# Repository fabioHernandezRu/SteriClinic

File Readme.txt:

Explicacion:

Actas= archivos de acta de entregables.
GUI = Ultima actualizacion de la GUI.
HWD = Descripcion de hardware del sistema.
Linux Directory = Directorio que debe ponerse en el Linux Root .
PCB = Ultimas actualizaciones de la PCB
Software = Version Funcional de la Autoclave Pequeña

Novedades:
La interaccion ARM - Nextion y ARM-FPGA con la GUI es funcional al 99%, lo que quiere decir que solo faltan pruebas del sistema para pruebas de funcionalidad.
Todas las Alarmas estan seteadas y funcionan, por hw y por sw. 
Modificaciones al Menu de Mantenimiento.
Modificaciones a animaciones del sitema.
Sonido al Boot de Inicio.
Integracion al Datalogger, lo que quiere decir q todas las variables de Nextion son almacenables por el ARM en disco.
Acceso al menu de mantenimiento con total control de todos los elementos de la board(Valvulas, sensores, etc).

Videos: 
 boot --> https://youtu.be/RCzLulutQhg 
	(Ver con sonido)
 Explicaciones
	1) https://youtu.be/06hYOt6X7v8 --> Intro ARM y Nextion
	2) https://youtu.be/eV6HMTO3BoQ --> Intro ARM y Nextion 2
	3) --> Como crear un nuevo proyecto en base de las librerias.
	4) --> Estructura de archivos de linux para Autoclaves

Pendientes:

1) pruebas de este entregable.

Otros Pendientes:
1) Pagina web.

Solicitud: 
Disponibilidad del Ing. Peter para guiarlo en el proceso de montaje de las tarjetas en la Autoclave pequeña y ademas de la prueba de control

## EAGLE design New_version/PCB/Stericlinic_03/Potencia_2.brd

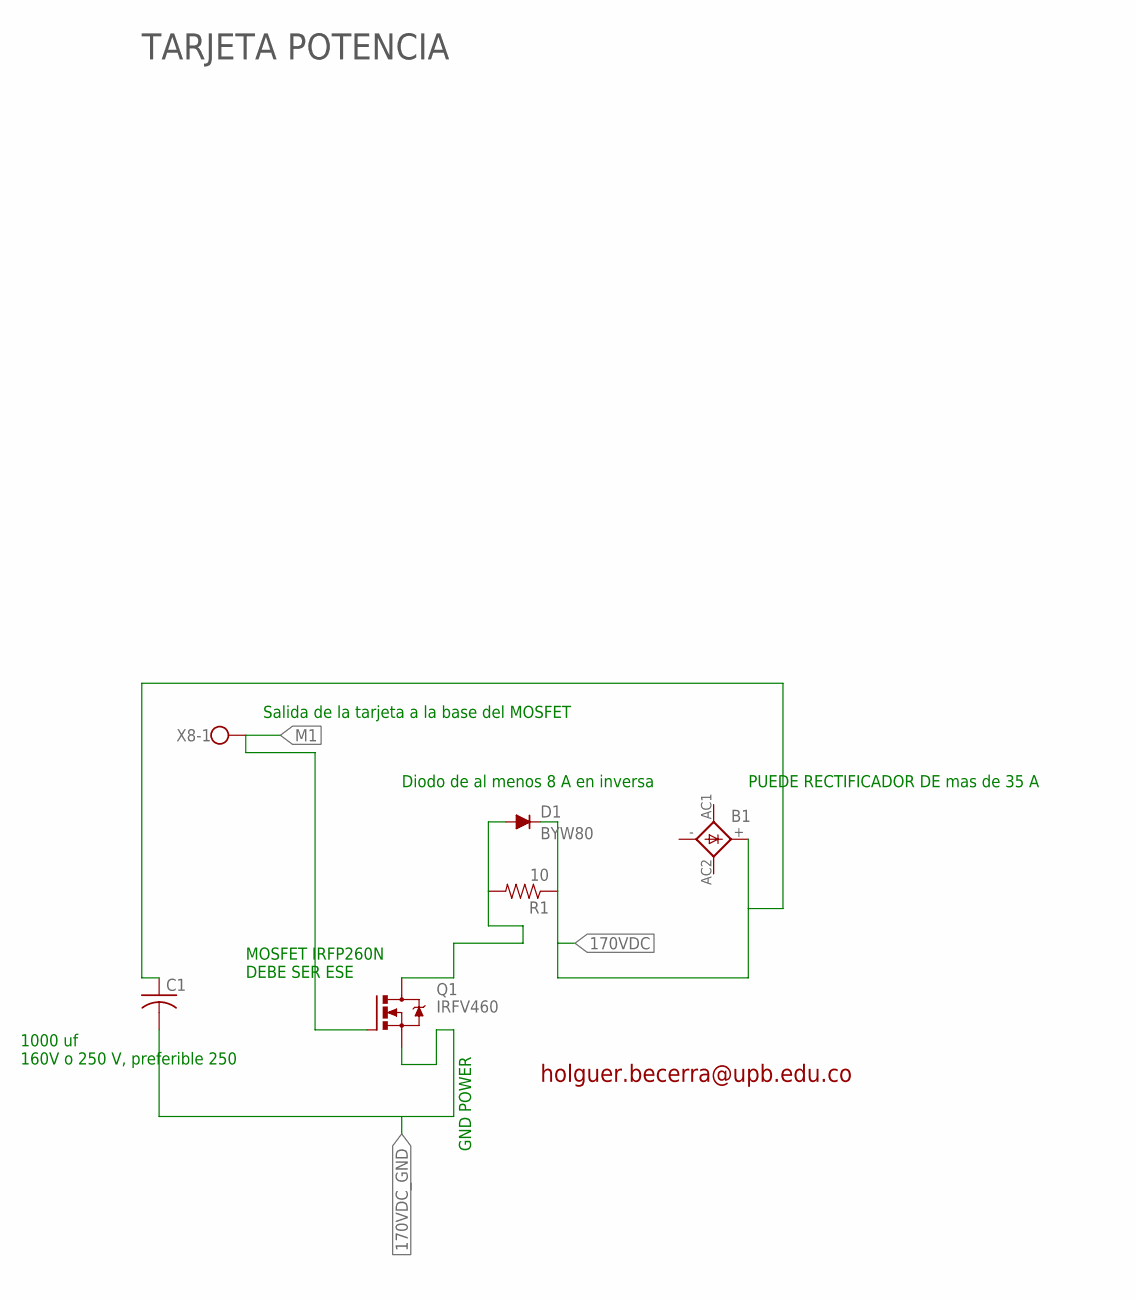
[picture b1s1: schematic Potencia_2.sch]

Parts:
B1: GBPC80X
C1: C-US275-205X316; C275-205X316
D1: BYW80; TO220ACS
Q1: IRFV460; TO258AA
R1: 10; 0603-RES
X8: CBE2; BE2

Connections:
170VDC: B1.+, C1.1, D1.C, R1.1
170VDC_GND: C1.2, Q1.2-S (S)
DAS: D1.A, Q1.1-D (D), R1.2
M1: Q1.3-G (G), X8.1

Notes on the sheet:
holguer.becerra@upb.edu.co
GND POWER
TARJETA POTENCIA
1000 uf 160V o 250 V, preferible 250
Diodo de al menos 8 A en inversa
MOSFET IRFP260N DEBE SER ESE
Salida de la tarjeta a la base del MOSFET
PUEDE RECTIFICADOR DE mas de 35 A

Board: 2 copper layers, 6 parts (0 on the bottom side), 4 nets, no tracks yet.

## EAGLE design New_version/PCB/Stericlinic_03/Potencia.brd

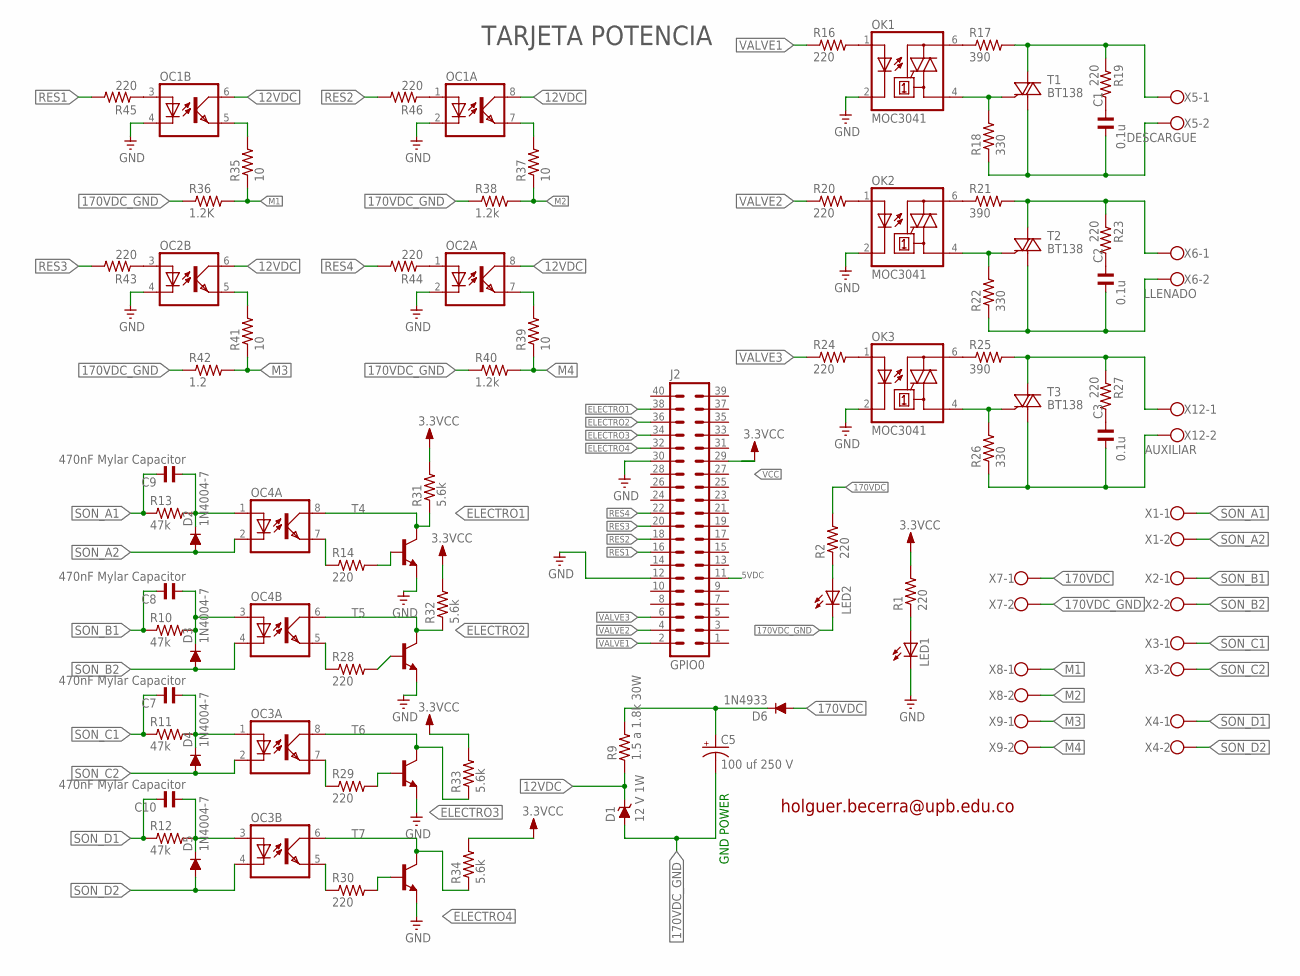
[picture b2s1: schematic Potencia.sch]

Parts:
C1, C2, C3: 0.1u; C075-042X103
C5: 100 uf 250 V; EB20D
C7, C8, C9, C10: 470nF Mylar Capacitor; C7.5B3
D1: 12 V 1W; C1702-15
D2, D3, D4, D5: 1N4004-7; DO41-7
D6: 1N4933; DO41-10
J2: GPIO0; ML40
LED1, LED2: LED3MM
OC1, OC2, OC3, OC4: ILD621; DIL08
OK1, OK2, OK3: MOC3041; DIL06
R1: 220; 0207/10
R2, R14, R16, R20, R24, R28, R29, R30, R43, R44, R45, R46: 220; 0207/7
R9: 1.5 a 1.8k 30W; CR15
R10, R11, R12, R13: 47k; 0207/7
R17, R21, R25: 390; 0207/2V
R18, R22, R26: 330; 0207/7
R19, R23, R27: 220; 0309V
R31, R32, R33, R34: 5.6k; 0207/7
R35, R37, R39, R41: 10; 0207/7
R36: 1.2K; 0207/7
R38, R40: 1.2k; 0207/7
R42: 1.2; 0207/7
T1, T2, T3: BT138; TO220BV
T4, T5, T6, T7: 2N2222-NPN-TO92-EBC; TO92-EBC
X1, X2, X3, X4, X7, X8, X9: CBE2; BE2
X5: DESCARGUE; BE2
X6: LLENADO; BE2
X12: AUXILIAR; BE2

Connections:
5VDC: J2.11
12VDC: D1.C, OC1.6 (COL), OC1.8 (COL), OC2.6 (COL), OC2.8 (COL), R9.1
170VDC: D6.A, R2.2, X7.1
170VDC_GND: C5.-, D1.A, LED2.K (C), R36.1, R38.1, R40.1, R42.1, X7.2
DAS: C5.+, D6.C, R9.2
ELECTRO1: J2.38, OC4.8 (COL), R31.1, T4.C
ELECTRO2: J2.36, OC4.6 (COL), R32.1, T5.C
ELECTRO3: J2.34, OC3.8 (COL), R33.1, T6.C
ELECTRO4: J2.32, OC3.6 (COL), R34.1, T7.C
GND: J2.12, J2.30, LED1.K (C), OC1.2 (C), OC1.4 (C), OC2.2 (C), OC2.4 (C), OK1.2 (C), OK2.2 (C), OK3.2 (C), T4.E, T5.E, T6.E, T7.E
M1: R35.1, R36.2, X8.1
M2: R37.1, R38.2, X8.2
M3: R41.1, R42.2, X9.1
M4: R39.1, R40.2, X9.2
unnamed: LED1.A, R1.1
unnamed: LED2.A, R2.1
unnamed: OK1.1 (A), R16.2
unnamed: OK2.1 (A), R20.2
unnamed: OK1.4 (A1), R18.2, T1.G
unnamed: OK1.6 (A2), R17.1
unnamed: R17.2, R19.1, T1.T2 (A2), X5.1
unnamed: C1.2, R18.1, T1.T1 (A1), X5.2
unnamed: C1.1, R19.2
unnamed: OK2.4 (A1), R22.2, T2.G
unnamed: OK2.6 (A2), R21.1
unnamed: R21.2, R23.1, T2.T2 (A2), X6.1
unnamed: C2.2, R22.1, T2.T1 (A1), X6.2
unnamed: C2.1, R23.2
unnamed: OK3.1 (A), R24.2
unnamed: OK3.4 (A1), R26.2, T3.G
unnamed: OK3.6 (A2), R25.1
unnamed: R25.2, R27.1, T3.T2 (A2), X12.1
unnamed: C3.2, R26.1, T3.T1 (A1), X12.2
unnamed: C3.1, R27.2
unnamed: C9.1, D2.C, OC4.1 (A), R13.2
unnamed: OC1.5 (EMIT), R35.2
unnamed: OC4.7 (EMIT), R14.1
unnamed: R14.2, T4.B
unnamed: OC2.5 (EMIT), R41.2
unnamed: OC2.3 (A), R43.1
unnamed: OC4.5 (EMIT), R28.1
unnamed: R28.2, T5.B
unnamed: OC3.7 (EMIT), R29.1
unnamed: R29.2, T6.B
unnamed: OC3.5 (EMIT), R30.1
unnamed: R30.2, T7.B
unnamed: OC1.3 (A), R45.1
unnamed: C8.1, D3.C, OC4.3 (A), R10.2
unnamed: OC1.1 (A), R46.1
unnamed: C7.1, D4.C, OC3.1 (A), R11.2
unnamed: OC2.1 (A), R44.1
unnamed: C10.1, D5.C, OC3.3 (A), R12.2
unnamed: OC2.7 (EMIT), R39.2
unnamed: OC1.7 (EMIT), R37.2
RES1: J2.16, R45.2
RES2: J2.18, R46.2
RES3: J2.20, R43.2
RES4: J2.22, R44.2
SON_A1: C9.2, R13.1, X1.1
SON_A2: D2.A, OC4.2 (C), X1.2
SON_B1: C8.2, R10.1, X2.1
SON_B2: D3.A, OC4.4 (C), X2.2
SON_C1: C7.2, R11.1, X3.1
SON_C2: D4.A, OC3.2 (C), X3.2
SON_D1: C10.2, R12.1, X4.1
SON_D2: D5.A, OC3.4 (C), X4.2
VALVE1: J2.2, R16.1
VALVE2: J2.4, R20.1
VALVE3: J2.6, R24.1
VCC: J2.29, R1.2, R31.2, R32.2, R33.2, R34.2

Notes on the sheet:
holguer.becerra@upb.edu.co
GND POWER
TARJETA POTENCIA

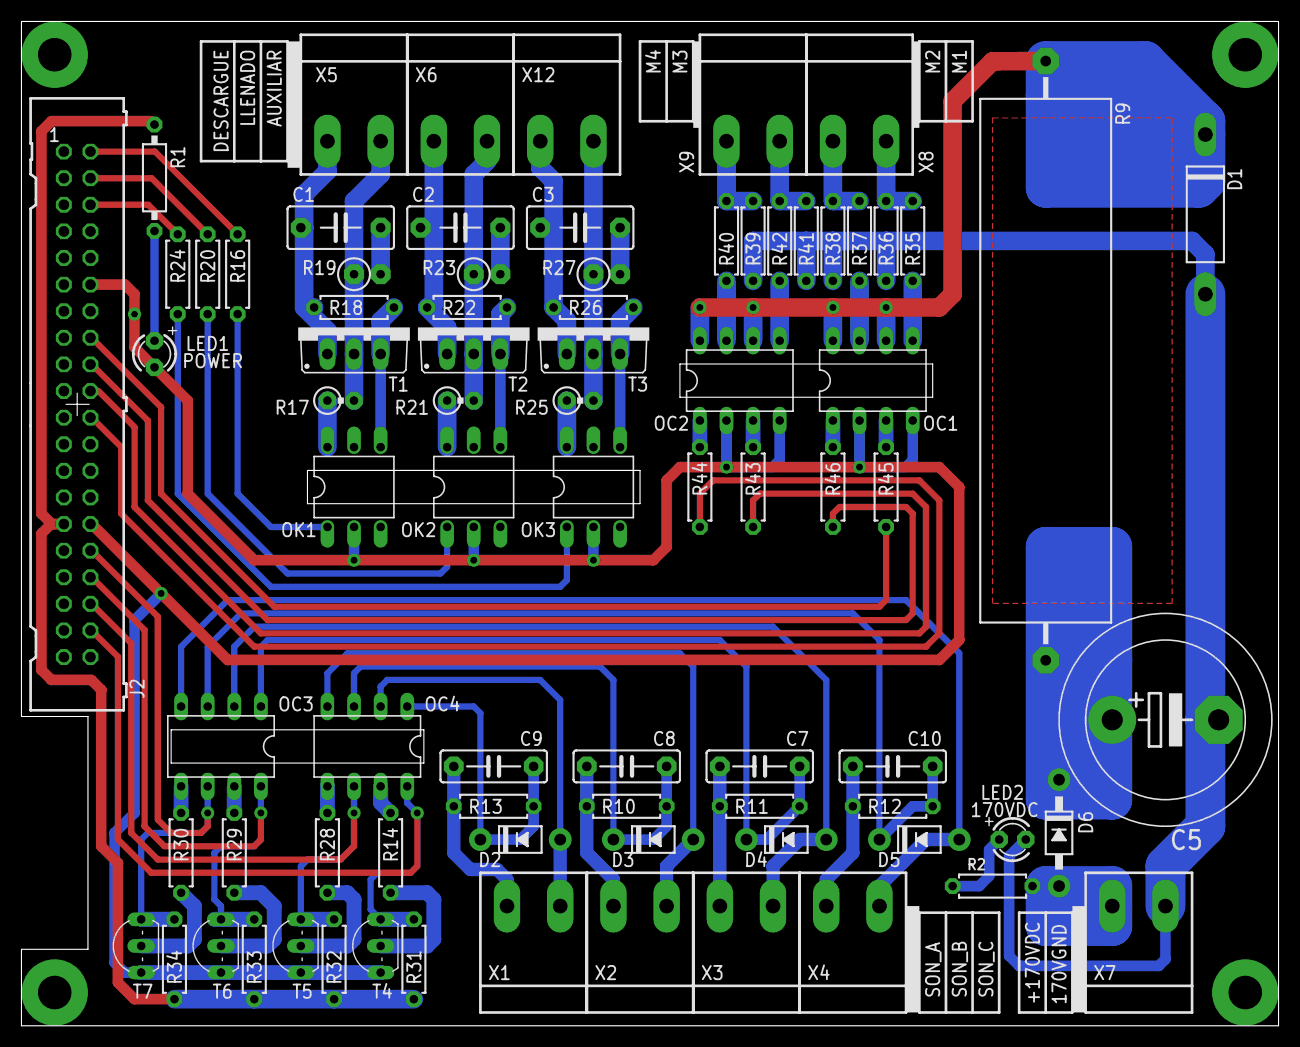
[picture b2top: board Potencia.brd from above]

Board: 2 copper layers, 120.0 x 95.9 mm, 80 parts (0 on the bottom side), 69 nets.

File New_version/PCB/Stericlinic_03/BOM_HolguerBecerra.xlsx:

Qty | Value | Device | Package | Parts
4 | 2N2222 | TRANSISTOR NPN | TO92-EBC | T4, T5, T6, T7
7 | CBE2 | BORNERA 2 PIN ENCHUFABLE | BE2 | X1, X2, X3, X4, X7, X8, X9
2 | LED | LED3MM | LED3MM | LED1, LED2
3 | 0.1u | C-US075-042X103 | C075-042X103 | C1, C2, C3
4 | 1.2K | R-US_0207/7 | 0207/7 | R36, R38, R40, R42
1 | 1.5 a 1.8k 30W | RCR15 | CR15 | R9
4 | 10 | R-US_0207/7 | 0207/7 | R35, R37, R39, R41
1 | 100 uf 250 V | CPOL-USE10-20 | EB20D | C5
1 | 10K | R-US_0207/7 | 0207/7 | R2
1 | 12 V 1W | ZENER-DIODEC1702-15 | C1702-15 | D1
4 | 1N4004-7 | 1N4004-7 | DO41-7 | D2, D3, D4, D5
1 | 1N4933 | 1N4933 | DO41-10 | D6
1 | 220 | R-US_0207/10 | 0207/10 | R1
11 | 220 | R-US_0207/7 | 0207/7 | R14, R16, R20, R24, R28, R29, R30, R43, R44, R45, R46
3 | 220 | R-US_0309/V | 0309V | R19, R23, R27
3 | 330 | R-US_0207/7 | 0207/7 | R18, R22, R26
3 | 390 | R-US_0207/2V | 0207/2V | R17, R21, R25
4 | 470nF/250V | C15/6 | C15B6 | C7, C8, C9, C10
4 | 47k | R-US_0207/7 | 0207/7 | R10, R11, R12, R13
4 | 5.6K | R-US_0207/7 | 0207/7 | R31, R32, R33, R34
1 | AUXILIAR | BONERA 2 PIN ENCHUFABLE | BE2 | X12
3 | BT138 | TRIAC | TO220BV | T1, T2, T3
1 | DESCARGUE | BONERA 2 PIN ENCHUFABLE | BE2 | X5
1 | GPIO0 | ML40 | ML40 | J2
1 | LLENADO | CBE2 | BE2 | X6
4 | MCT6 | PS2501-2 | DIL08 | OC1, OC2, OC3, OC4
3 | MOC3041 | MOC3041M | DIL06 | OK1, OK2, OK3

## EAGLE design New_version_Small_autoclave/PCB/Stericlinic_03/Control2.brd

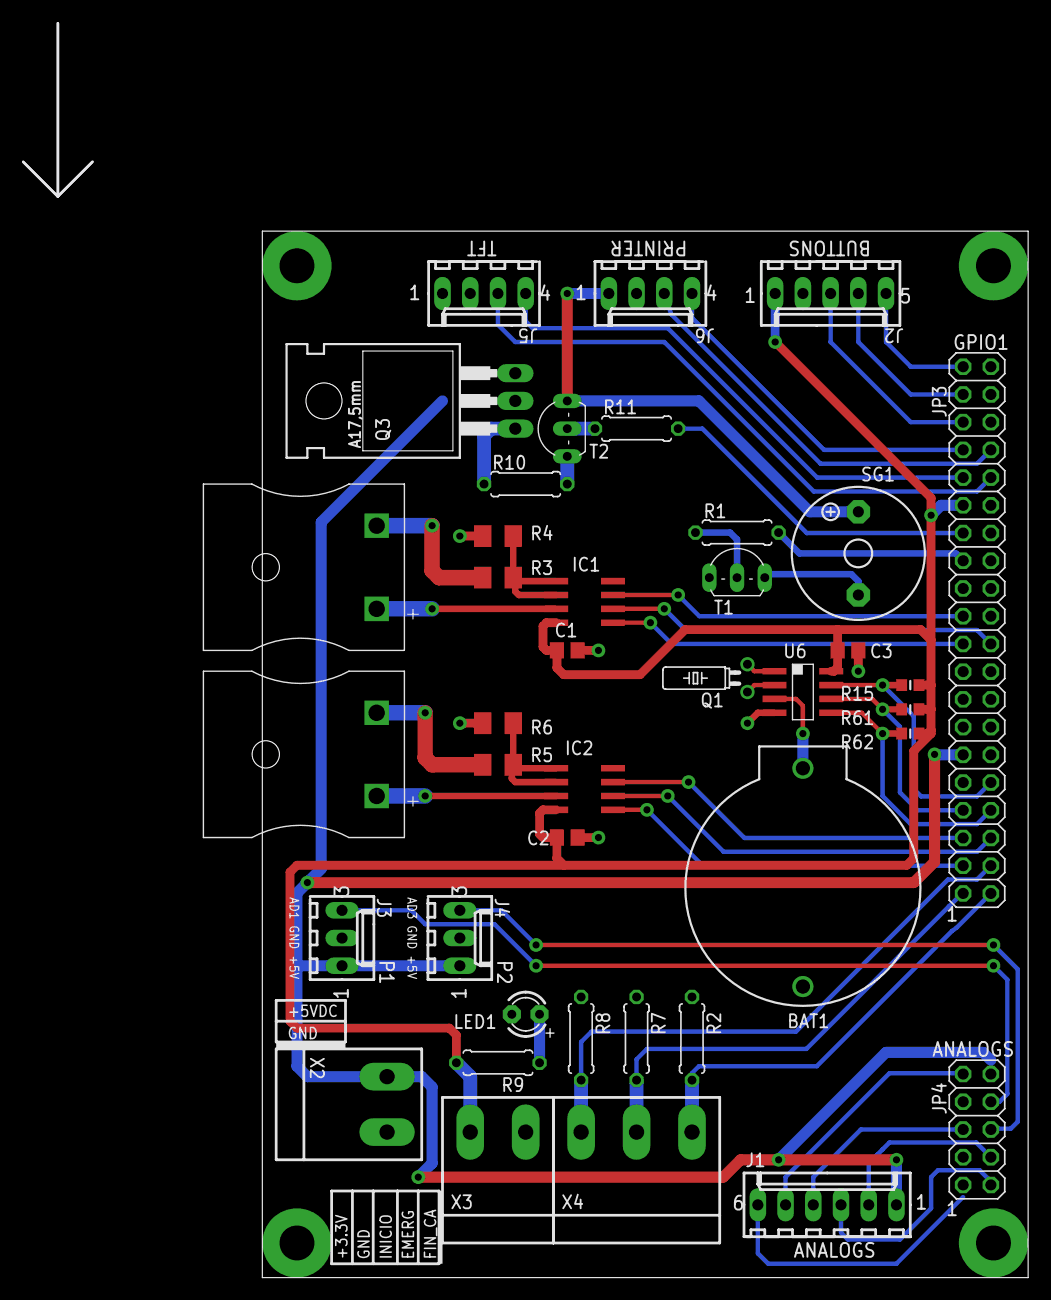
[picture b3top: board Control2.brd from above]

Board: 2 copper layers, 70.2 x 95.9 mm, 40 parts (0 on the bottom side), 45 nets.

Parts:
BAT1: CR2032; BATTCOM_20MM_PTH
C1, C2, C3: 104; C0805
IC1, IC2: MAX6675; SO08
J1: ANALOGS; 6410-06
J2: BUTTONS; 6410-05
J3: P1; 6410-03
J4: P2; 6410-03
J5: TFT; 6410-04
J6: PRINTER; 6410-04
JP3: GPIO1; 2X20
JP4: ADC; 2X05
LED1: POWER; LED3MM
Q1: 32768Hz; TC26H
Q3: 2N5496; TO220
R1, R9, R10, R11: 220; 0207/7
R2, R7, R8: 5k; 0207/7
R3, R4, R5, R6: 0R; M1206
R15, R61, R62: 10K; R0603
SG1: F/TMB
T1, T2: 2N2222; TO92-EBC
U6: DS1338; SO08
U$1, U$4: THERMOCOUPLEPLUG_MINI; TC-MINI
X2: POWER; BE2
X3: +3V3-GND; BE2
X4: SIGNALS; BE3

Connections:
5VCC: J1.1, J3.1, J4.1, J6.1, JP3.12, SG1.+, T2.C, X2.1
+3V3: C1.1, C2.1, C3.1, IC1.4, IC2.4, J2.1, JP3.30, R9.2, R15.1, R61.1, R62.1, U6.8, X3.1
ADC_0: J1.5, JP4.10
ADC_1: J3.3, JP4.7
ADC_3: J4.3, JP4.5
ADC_4: J1.4, JP4.6
ADC_5: J1.2, JP4.3
ADC_7: J1.3, JP4.1
ALARM: JP3.26, R1.1
EMERGENCIA: JP3.2, R7.2, X4.2
FINAL_CARRERA: JP3.1, R2.2, X4.3
GND: BAT1.2, C1.2, C2.2, C3.2, J1.6, J2.2, J3.2, J4.2, J6.2, JP3.11, JP3.29, LED1.K, Q3.3, R2.1, R4.2, R6.2, R7.1, R8.1, T1.E, U6.4, X2.2, X3.2
INICIO: JP3.3, R8.2, X4.1
unnamed: Q1.2, U6.1
unnamed: LED1.A, R9.1
unnamed: SG1.-, T1.C
unnamed: R1.2, T1.B
unnamed: IC1.3, U$1.+
unnamed: R5.1, U$4.-
unnamed: IC2.3, U$4.+
unnamed: Q1.1, U6.2
unnamed: R10.1, T2.E
unnamed: R3.1, U$1.-
unnamed: Q3.1, R10.2
unnamed: R11.2, T2.B
unnamed: IC2.1, IC2.2, R5.2, R6.1
unnamed: IC1.1, IC1.2, R3.2, R4.1
unnamed: BAT1.1, U6.3
ON_SCREEN: JP3.28, R11.1
OP1: J2.3, JP3.36
OP2: J2.4, JP3.38
OP3: J2.5, JP3.40
PRINTER_RX: J6.3, JP3.33
PRINTER_TX: J6.4, JP3.34
RTC_SCL: JP3.8, R61.2, U6.6
RTC_SDA: JP3.7, R62.2, U6.5
RTC_WQ: JP3.9, R15.2, U6.7
TE1_CLK: IC1.5, JP3.20
TE1_CS: IC1.6, JP3.19
TE1_MISO: IC1.7, JP3.22
TE2_CLK: IC2.5, JP3.4
TE2_CS: IC2.6, JP3.5
TE2_MISO: IC2.7, JP3.6
TFT_RX: J5.3, JP3.31
TFT_TX: J5.4, JP3.32

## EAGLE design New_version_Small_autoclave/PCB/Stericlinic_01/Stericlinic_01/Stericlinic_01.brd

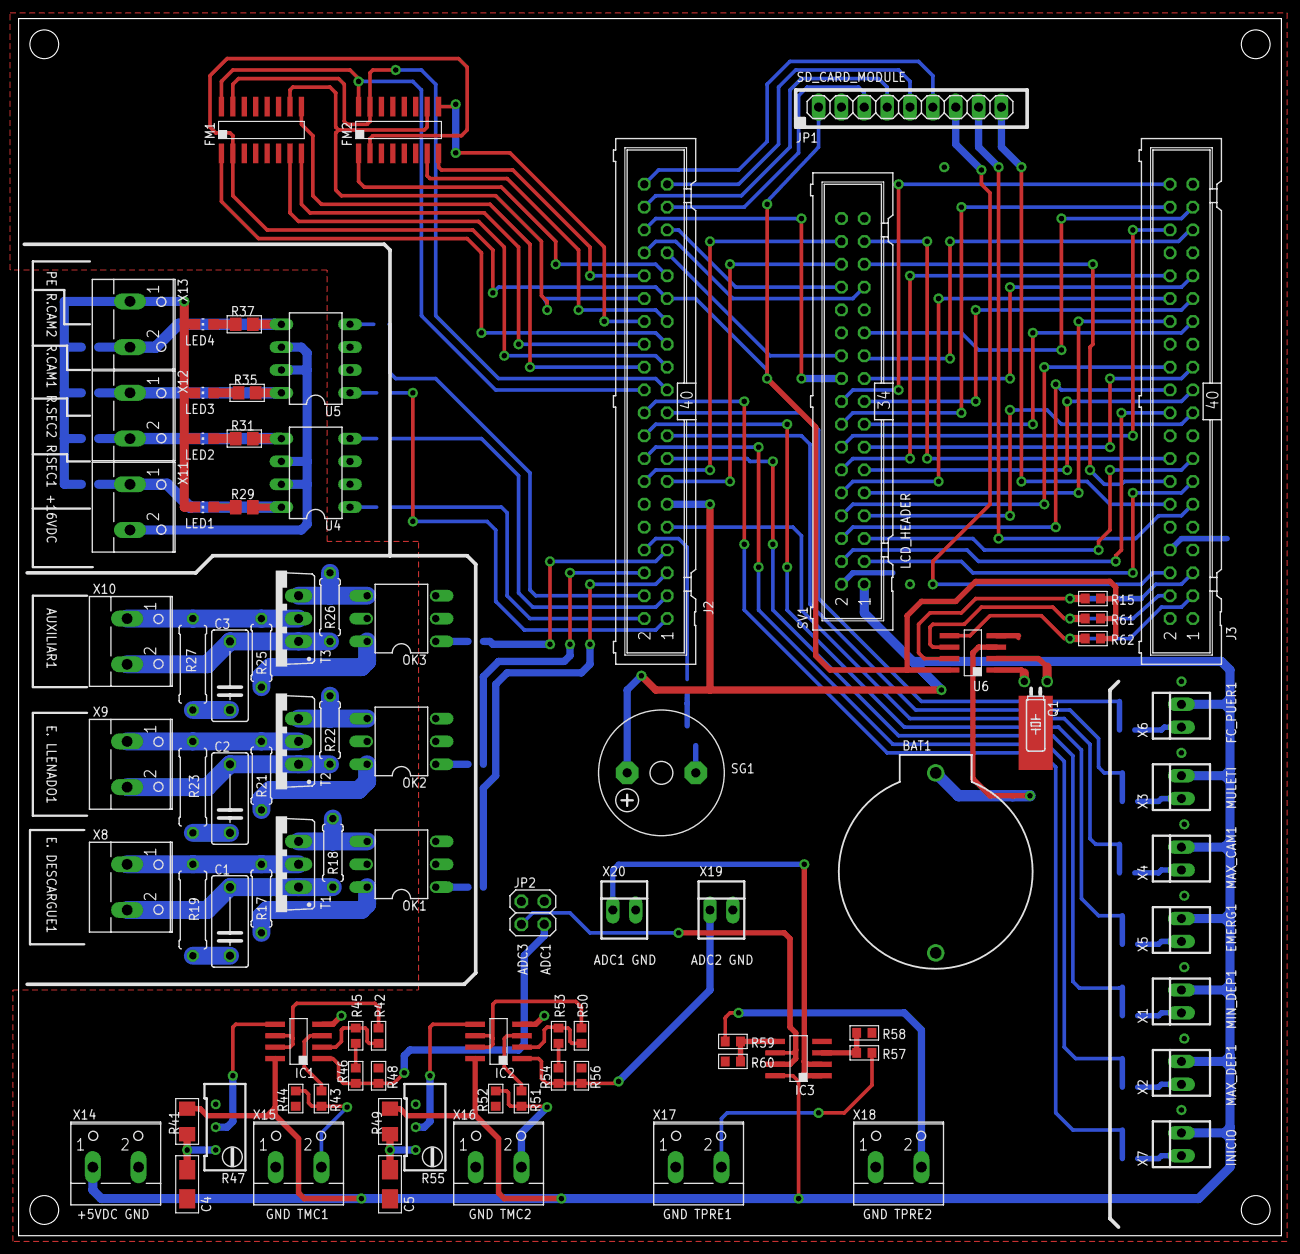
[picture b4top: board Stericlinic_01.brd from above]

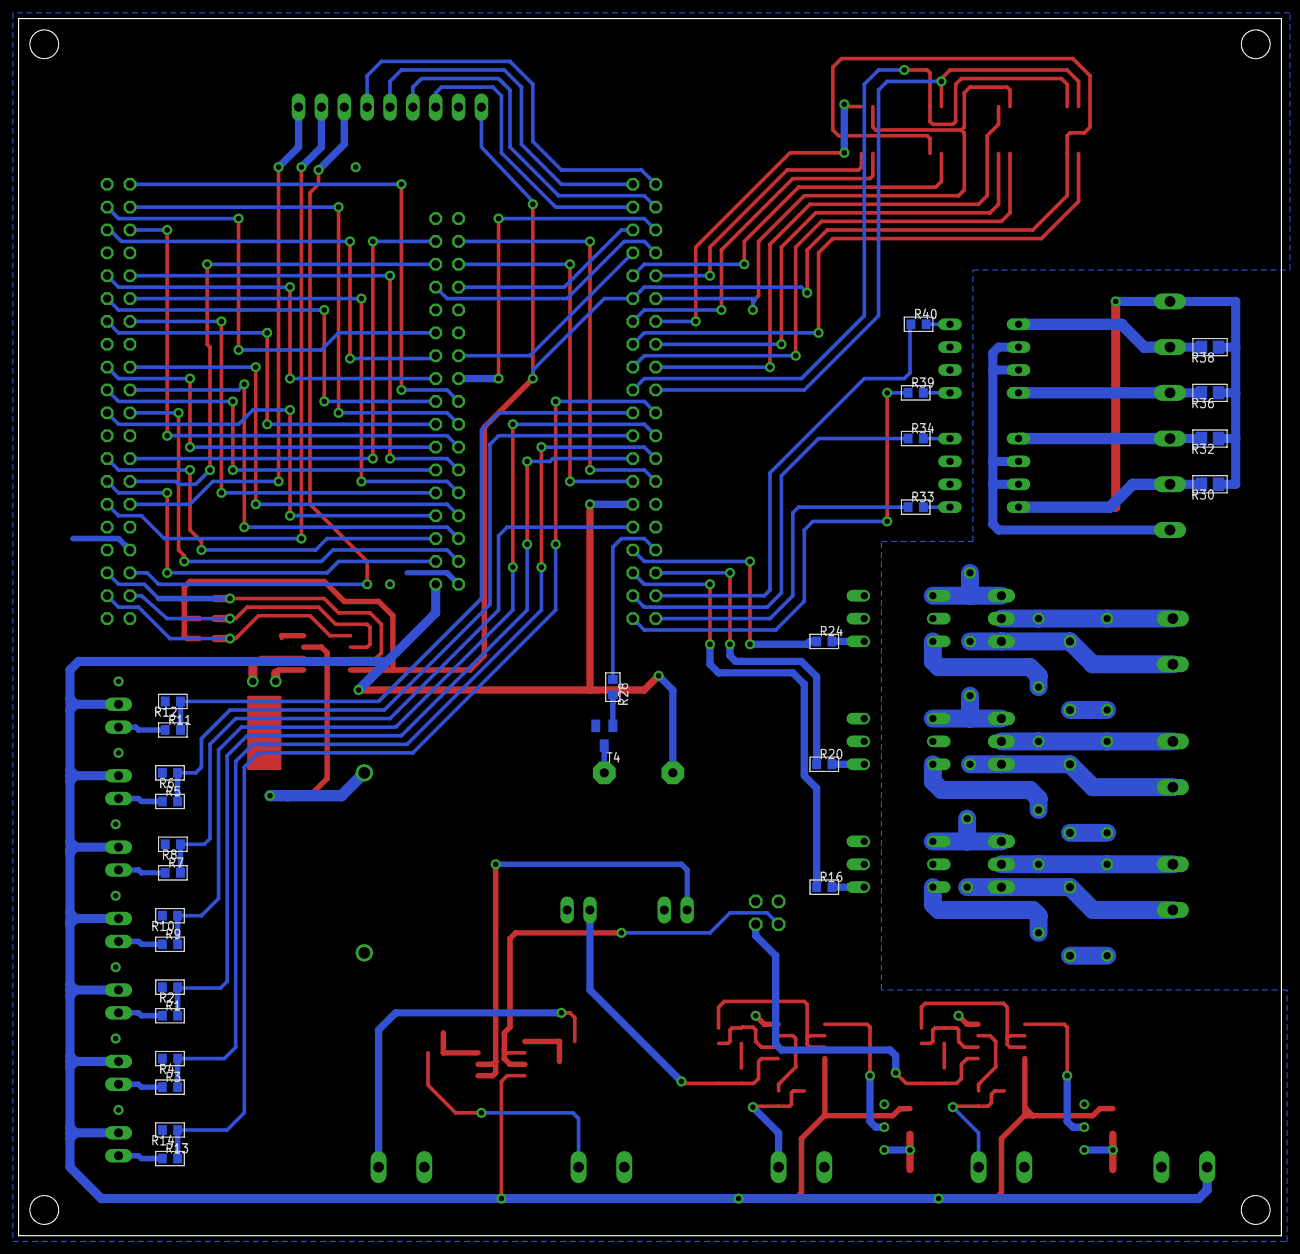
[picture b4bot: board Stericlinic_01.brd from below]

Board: 2 copper layers, 140.3 x 135.3 mm, 114 parts (27 on the bottom side), 131 nets.

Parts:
BAT1: BATTCOM_20MM_PTH
C1, C2, C3: 0.1u; C075-042X103
C4, C5: 1u; B/3528-21W
FM1, FM2: S25FL064P; SO16
IC1, IC2, IC3: LM358D; SO08
J2, J3: ML40
JP1: SDCARD1; 1X09
JP2: 2X02
LED1, LED2, LED3, LED4: CHIP-LED0805
OK1, OK2, OK3: MOC3041; DIL06
Q1: TC26H
R1, R3, R5, R7, R9, R11, R13, R15, R48, R56, R57, R59, R61, R62: 10K; R0603
R2, R4, R6, R8, R10, R12, R14, R58, R60: 20K; R0603
R16, R20, R24, R28, R33, R34, R39, R40: 220; R0603
R17, R21, R25: 390; 0207/7
R18, R22, R26: 330; 0207/7
R19, R23, R27: 220; 0309/10
R29: 1K; M0805
R30, R32, R36, R38: 10K; R0805
R31, R35, R37: 1K; R0805
R41, R49: 5K; R1206
R42, R50: 820; R0603
R43, R51: 470; R0603
R44, R52: 135; R0603
R45, R53: 330; R0603
R46, R54: 130; R0603
R47, R55: 10K; RTRIM64W
SG1: F/CM12P
SV1: LCD_HEADER1; ML34
T1, T2, T3: BT138; TO220BV
T4: SOT23-BEC
U4, U5: ILD74; DIL08
U6: DS1338; SO08
X1: NIVEL_MIN_DEP1; 22-23-2021
X2: NIVEL_MAX_DEP1; 22-23-2021
X3: MULETILLA_ON/OFF; 22-23-2021
X4: NIVEL_MAX_CAM1; 22-23-2021
X5: EMERGENCIA1; 22-23-2021
X6: FINAL_CARRERA_PUERTA1; 22-23-2021
X7: BOTON_INICIO; 22-23-2021
X8: E. DESCARGUE1; W237-102
X9: E. LLENADO1; W237-102
X10: AUXILIAR1; W237-102
X11, X12, X13: W237-102
X14: POWER; W237-102
X15: TERMOCUPLA1; W237-102
X16: TERMOCUPLA2; W237-102
X17: T_PRESION1; W237-102
X18: T_PRESION2; W237-102
X19: ADC2; 22-23-2021
X20: ADC1; 22-23-2021

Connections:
+3V3: FM1.2, FM2.2, J2.29, JP1.1, R15.1, R61.1, R62.1, U6.8
+5V: IC1.8, IC2.8, IC3.8, J2.11, R41.2, R49.2, SG1.+, SV1.1, X1.2, X2.2, X3.2, X4.2, X5.2, X6.2, X7.2, X14.1
+16VDC: U4.6, U4.7, U5.6, U5.7, X11.2
ADC1: IC1.1, JP2.1, R46.2, R48.2
ADC2: IC2.1, R54.2, R56.2, X19.1
ADC3: IC3.6, IC3.7, JP2.2
DIFF_RX_0+: J2.39, JP1.5
DIFF_RX_0-: J2.40, JP1.6
DIFF_RX_1+: J2.37, JP1.3
DIFF_RX_1-: J2.38, JP1.4
DIFF_RX_4+: FM2.1, J2.31
DIFF_RX_4-: FM2.8, J2.32
DIFF_RX_5+: FM2.7, J2.27
DIFF_RX_5-: FM2.9, J2.28
DIFF_RX_6+: FM1.1, J2.25
DIFF_RX_6-: FM1.8, J2.26
DIFF_RX_7+: FM1.7, J2.23
DIFF_RX_7-: FM1.9, J2.24
DIFF_RX_8+: FM1.15, FM2.15, J2.21
DIFF_RX_8-: FM1.16, FM2.16, J2.22
DIFF_RX_9+: J2.19, R11.2, R12.1
DIFF_RX_9-: J2.20, R13.2, R14.1
DIFF_RX_A+: J2.17, R5.2, R6.1
DIFF_RX_A-: J2.18, R9.2, R10.1
DIFF_RX_B+: J2.15, R1.2, R2.1
DIFF_RX_B-: J2.16, R3.2, R4.1
GND: BAT1.2, C4.-, C5.-, FM1.10, FM2.10, IC1.4, IC2.4, IC3.4, J2.12, J2.30, J3.8, JP1.2, JP2.3, JP2.4, OK1.2, OK2.2, OK3.2, R2.2, R4.2, R6.2, R8.2, R10.2, R12.2, R14.2, R44.1, R47.1, R48.1, R52.1, R55.1, R56.1, R58.1, R60.1, SV1.2, T4.E, U4.2, U4.3, U5.2, U5.3, U6.4, X14.2, X15.1, X16.1, X17.1, X18.1, X19.2, X20.2
GPIO01: J2.1, R39.1
GPIO02: J2.2, R33.1
GPIO03: J2.3, R34.1
GPIO04: J2.4, R40.1
GPIO05: J2.5, R16.1
GPIO06: J2.6, R20.1
GPIO07: J2.7, R24.1
GPIO08: J2.8, R28.1
GPIO09: J2.9, R7.2, R8.1
GPIOA: J3.5, R15.2, U6.7
GPIOB: J3.6, JP1.7
I2C_SCL: J3.4, R61.2, U6.6
I2C_SDA: J3.3, R62.2, U6.5
LCD_BLCNT: J2.34, SV1.27
LCD_CS: J3.31, SV1.19
LCD_DB0: J3.13, SV1.3
LCD_DB1: J3.20, SV1.4
LCD_DB2: J3.15, SV1.5
LCD_DB3: J3.22, SV1.6
LCD_DB4: J3.19, SV1.7
LCD_DB5: J3.24, SV1.8
LCD_DB6: J3.28, SV1.9
LCD_DB7: J3.30, SV1.10
LCD_DB8: J3.21, SV1.11
LCD_DB9: J3.32, SV1.12
LCD_DB10: J3.23, SV1.13
LCD_DB11: J3.36, SV1.14
LCD_DB12: J3.27, SV1.15
LCD_DB13: J3.38, SV1.16
LCD_DB14: J3.29, SV1.17
LCD_DB15: J3.40, SV1.18
LCD_RD: J2.33, SV1.22
LCD_RESET: J3.37, SV1.23
LCD_RS: J2.36, SV1.20
LCD_WR: J3.35, SV1.21
LVDS_TX_B+: J3.12, JP1.9
LVDS_TX_B-: J3.11, JP1.8
unnamed: Q1.2, U6.1
unnamed: R1.1, X1.1
unnamed: R3.1, X2.1
unnamed: R5.1, X3.1
unnamed: R7.1, X4.1
unnamed: R9.1, X5.1
unnamed: R11.1, X6.1
unnamed: R13.1, X7.1
unnamed: Q1.1, U6.2
unnamed: OK1.1, R16.2
unnamed: R28.2, T4.B
unnamed: OK2.1, R20.2
unnamed: OK1.4, R18.2, T1.G
unnamed: OK1.6, R17.1
unnamed: R17.2, R19.1, T1.T2, X8.1
unnamed: C1.2, R18.1, T1.T1, X8.2
unnamed: C1.1, R19.2
unnamed: OK2.4, R22.2, T2.G
unnamed: OK2.6, R21.1
unnamed: R21.2, R23.1, T2.T2, X9.1
unnamed: C2.2, R22.1, T2.T1, X9.2
unnamed: C2.1, R23.2
unnamed: OK3.1, R24.2
unnamed: OK3.4, R26.2, T3.G
unnamed: OK3.6, R25.1
unnamed: R25.2, R27.1, T3.T2, X10.1
unnamed: C3.2, R26.1, T3.T1, X10.2
unnamed: C3.1, R27.2
unnamed: SG1.-, T4.C
unnamed: C4.+, R41.1, R47.3
unnamed: R33.2, U4.1
unnamed: LED1.A, R29.1
unnamed: LED2.A, R31.1
unnamed: R34.2, U4.4
unnamed: BAT1.1, U6.3
unnamed: IC1.5, R47.2
unnamed: LED3.A, R35.1
unnamed: LED4.A, R37.1
unnamed: R39.2, U5.1
unnamed: R40.2, U5.4
unnamed: IC1.6, IC1.7, R42.1
unnamed: IC1.2, R42.2, R45.1
unnamed: R45.2, R46.1
unnamed: R43.1, R44.2, X15.2
unnamed: IC3.3, R57.2, R58.2
unnamed: IC1.3, R43.2
unnamed: C5.+, R49.1, R55.3
unnamed: IC2.5, R55.2
unnamed: IC2.6, IC2.7, R50.1
unnamed: IC2.2, R50.2, R53.1
unnamed: R53.2, R54.1
unnamed: R51.1, R52.2, X16.2
unnamed: IC2.3, R51.2
unnamed: IC3.1, IC3.2, X20.1
unnamed: R57.1, X17.2
unnamed: IC3.5, R59.2, R60.2
unnamed: R59.1, X18.2
PE: LED1.C, LED2.C, LED3.C, LED4.C, R30.1, R32.1, R36.1, R38.1, X13.1
R_CAMARA1: R35.2, R36.2, U5.8, X12.1
R_CAMARA2: R37.2, R38.2, U5.5, X13.2
R_SECADO1: R29.2, R30.2, U4.8, X11.1
R_SECADO2: R31.2, R32.2, U4.5, X12.2
TP_CS: J3.14, SV1.29
TP_IRQ: J2.35, SV1.28
TP_SCK: J2.13, SV1.30
TP_SI: J3.16, SV1.31
TP_SO: J2.14, SV1.32

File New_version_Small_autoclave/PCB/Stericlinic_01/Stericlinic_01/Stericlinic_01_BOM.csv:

Part;Value;Device;Package;Description
BAT1;;BATTERY20PTH;BATTCOM_20MM_PTH;Battery Holders
C1;0.1u;C-US075-042X103;C075-042X103;CAPACITOR, American symbol
C2;0.1u;C-US075-042X103;C075-042X103;CAPACITOR, American symbol
C3;0.1u;C-US075-042X103;C075-042X103;CAPACITOR, American symbol
C4;1u;CPOL-USB/3528-21W;B/3528-21W;POLARIZED CAPACITOR, American symbol
C5;1u;CPOL-USB/3528-21W;B/3528-21W;POLARIZED CAPACITOR, American symbol
FM1;S25FL064P;S25FL064P;SO16;
FM2;S25FL064P;S25FL064P;SO16;
IC1;LM358D;LM358D;SO08;"OP AMP also LM158; LM258; LM2904"
IC2;LM358D;LM358D;SO08;"OP AMP also LM158; LM258; LM2904"
IC3;LM358D;LM358D;SO08;"OP AMP also LM158; LM258; LM2904"
J2;;ML40;ML40;HARTING
J3;;ML40;ML40;HARTING
JP1;SDCARD1;PINHD-1X9;1X09;PIN HEADER
JP2;;PINHD-2X2;2X02;PIN HEADER
LED1;;LEDCHIP-LED0805;CHIP-LED0805;LED
LED2;;LEDCHIP-LED0805;CHIP-LED0805;LED
LED3;;LEDCHIP-LED0805;CHIP-LED0805;LED
LED4;;LEDCHIP-LED0805;CHIP-LED0805;LED
OK1;MOC3041;MOC3041M;DIL06;6-Pin DIP Zero-Cross Optoisolators Triac Driver Output (250/400 Volt Peak)
OK2;MOC3041;MOC3041M;DIL06;6-Pin DIP Zero-Cross Optoisolators Triac Driver Output (250/400 Volt Peak)
OK3;MOC3041;MOC3041M;DIL06;6-Pin DIP Zero-Cross Optoisolators Triac Driver Output (250/400 Volt Peak)
Q1;;CRYSTALTC26H;TC26H;CRYSTAL
R1;10K;R-US_R0603;R0603;RESISTOR, American symbol
R2;20K;R-US_R0603;R0603;RESISTOR, American symbol
R3;10K;R-US_R0603;R0603;RESISTOR, American symbol
R4;20K;R-US_R0603;R0603;RESISTOR, American symbol
R5;10K;R-US_R0603;R0603;RESISTOR, American symbol
R6;20K;R-US_R0603;R0603;RESISTOR, American symbol
R7;10K;R-US_R0603;R0603;RESISTOR, American symbol
R8;20K;R-US_R0603;R0603;RESISTOR, American symbol
R9;10K;R-US_R0603;R0603;RESISTOR, American symbol
R10;20K;R-US_R0603;R0603;RESISTOR, American symbol
R11;10K;R-US_R0603;R0603;RESISTOR, American symbol
R12;20K;R-US_R0603;R0603;RESISTOR, American symbol
R13;10K;R-US_R0603;R0603;RESISTOR, American symbol
R14;20K;R-US_R0603;R0603;RESISTOR, American symbol
R15;10K;R-US_R0603;R0603;RESISTOR, American symbol
R16;220;R-US_R0603;R0603;RESISTOR, American symbol
R17;390;R-US_0207/7;0207/7;RESISTOR, American symbol
R18;330;R-US_0207/7;0207/7;RESISTOR, American symbol
R19;220;R-US_0309/10;0309/10;RESISTOR, American symbol
R20;220;R-US_R0603;R0603;RESISTOR, American symbol
R21;390;R-US_0207/7;0207/7;RESISTOR, American symbol
R22;330;R-US_0207/7;0207/7;RESISTOR, American symbol
R23;220;R-US_0309/10;0309/10;RESISTOR, American symbol
R24;220;R-US_R0603;R0603;RESISTOR, American symbol
R25;390;R-US_0207/7;0207/7;RESISTOR, American symbol
R26;330;R-US_0207/7;0207/7;RESISTOR, American symbol
R27;220;R-US_0309/10;0309/10;RESISTOR, American symbol
R28;220;R-US_R0603;R0603;RESISTOR, American symbol
R29;1K;R-US_M0805;M0805;RESISTOR, American symbol
R30;10K;R-US_R0805;R0805;RESISTOR, American symbol
R31;1K;R-US_R0805;R0805;RESISTOR, American symbol
R32;10K;R-US_R0805;R0805;RESISTOR, American symbol
R33;220;R-US_R0603;R0603;RESISTOR, American symbol
R34;220;R-US_R0603;R0603;RESISTOR, American symbol
R35;1K;R-US_R0805;R0805;RESISTOR, American symbol
R36;10K;R-US_R0805;R0805;RESISTOR, American symbol
R37;1K;R-US_R0805;R0805;RESISTOR, American symbol
R38;10K;R-US_R0805;R0805;RESISTOR, American symbol
R39;220;R-US_R0603;R0603;RESISTOR, American symbol
R40;220;R-US_R0603;R0603;RESISTOR, American symbol
R41;5K;R-US_R1206;R1206;RESISTOR, American symbol
R42;820;R-US_R0603;R0603;RESISTOR, American symbol
R43;470;R-US_R0603;R0603;RESISTOR, American symbol
R44;135;R-US_R0603;R0603;RESISTOR, American symbol
R45;330;R-US_R0603;R0603;RESISTOR, American symbol
R46;130;R-US_R0603;R0603;RESISTOR, American symbol
R47;10K;R-TRIMM64W;RTRIM64W;Trimm resistor
R48;10K;R-US_R0603;R0603;RESISTOR, American symbol
R49;5K;R-US_R1206;R1206;RESISTOR, American symbol
R50;820;R-US_R0603;R0603;RESISTOR, American symbol
R51;470;R-US_R0603;R0603;RESISTOR, American symbol
R52;135;R-US_R0603;R0603;RESISTOR, American symbol
R53;330;R-US_R0603;R0603;RESISTOR, American symbol
R54;130;R-US_R0603;R0603;RESISTOR, American symbol
R55;10K;R-TRIMM64W;RTRIM64W;Trimm resistor
R56;10K;R-US_R0603;R0603;RESISTOR, American symbol
R57;10K;R-US_R0603;R0603;RESISTOR, American symbol
R58;20K;R-US_R0603;R0603;RESISTOR, American symbol
R59;10K;R-US_R0603;R0603;RESISTOR, American symbol
R60;20K;R-US_R0603;R0603;RESISTOR, American symbol
R61;10K;R-US_R0603;R0603;RESISTOR, American symbol
R62;10K;R-US_R0603;R0603;RESISTOR, American symbol
SG1;F/CM12P;F/CM12P;F/CM12P;BUZZER Source: Buerklin
SV1;LCD_HEADER1;ML34;ML34;HARTING
T1;BT138;BT138-V;TO220BV;TRIAC
T2;BT138;BT138-V;TO220BV;TRIAC
T3;BT138;BT138-V;TO220BV;TRIAC
T4;;MMBT2222ALT1-NPN-SOT23-BEC;SOT23-BEC;NPN Transistror
U4;ILD74;ILD74;DIL08;
U5;ILD74;ILD74;DIL08;
U6;DS1338;DS1338;SO08;
X1;NIVEL_MIN_DEP1;22-23-2021;22-23-2021;".100 (2.54mm) Center Header - 2 Pin"""
X2;NIVEL_MAX_DEP1;22-23-2021;22-23-2021;".100 (2.54mm) Center Header - 2 Pin"""
X3;MULETILLA_ON/OFF;22-23-2021;22-23-2021;".100 (2.54mm) Center Header - 2 Pin"""
X4;NIVEL_MAX_CAM1;22-23-2021;22-23-2021;".100 (2.54mm) Center Header - 2 Pin"""
X5;EMERGENCIA1;22-23-2021;22-23-2021;".100 (2.54mm) Center Header - 2 Pin"""
X6;FINAL_CARRERA_PUERTA1;22-23-2021;22-23-2021;".100 (2.54mm) Center Header - 2 Pin"""
X7;BOTON_INICIO;22-23-2021;22-23-2021;".100 (2.54mm) Center Header - 2 Pin"""
X8;E. DESCARGUE1;W237-102;W237-102;WAGO SCREW CLAMP
X9;E. LLENADO1;W237-102;W237-102;WAGO SCREW CLAMP
X10;AUXILIAR1;W237-102;W237-102;WAGO SCREW CLAMP
X11;;W237-102;W237-102;WAGO SCREW CLAMP
X12;;W237-102;W237-102;WAGO SCREW CLAMP
X13;;W237-102;W237-102;WAGO SCREW CLAMP
X14;POWER;W237-102;W237-102;WAGO SCREW CLAMP
X15;TERMOCUPLA1;W237-102;W237-102;WAGO SCREW CLAMP
X16;TERMOCUPLA2;W237-102;W237-102;WAGO SCREW CLAMP
X17;T_PRESION1;W237-102;W237-102;WAGO SCREW CLAMP
X18;T_PRESION2;W237-102;W237-102;WAGO SCREW CLAMP
X19;ADC2;22-23-2021;22-23-2021;".100 (2.54mm) Center Header - 2 Pin"""
X20;ADC1;22-23-2021;22-23-2021;".100 (2.54mm) Center Header - 2 Pin"""

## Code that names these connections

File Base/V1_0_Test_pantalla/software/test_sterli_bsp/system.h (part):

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#define LCD_CS_IRQ -1
#define LCD_CS_IRQ_INTERRUPT_CONTROLLER_ID -1
#define LCD_CS_IRQ_TYPE "NONE"
#define LCD_CS_NAME "/dev/lcd_cs"
#define LCD_CS_RESET_VALUE 0
#define LCD_CS_SPAN 16
#define LCD_CS_TYPE "altera_avalon_pio"
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#define LCD_RD_IRQ -1
#define LCD_RD_IRQ_INTERRUPT_CONTROLLER_ID -1
#define LCD_RD_IRQ_TYPE "NONE"
#define LCD_RD_NAME "/dev/lcd_rd"
#define LCD_RD_RESET_VALUE 0
#define LCD_RD_SPAN 16
#define LCD_RD_TYPE "altera_avalon_pio"
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#define LCD_RS_IRQ -1
#define LCD_RS_IRQ_INTERRUPT_CONTROLLER_ID -1
#define LCD_RS_IRQ_TYPE "NONE"
#define LCD_RS_NAME "/dev/lcd_rs"
#define LCD_RS_RESET_VALUE 0
#define LCD_RS_SPAN 16
#define LCD_RS_TYPE "altera_avalon_pio"
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#define LCD_WR_IRQ -1
#define LCD_WR_IRQ_INTERRUPT_CONTROLLER_ID -1
#define LCD_WR_IRQ_TYPE "NONE"
#define LCD_WR_NAME "/dev/lcd_wr"
#define LCD_WR_RESET_VALUE 0
#define LCD_WR_SPAN 16
#define LCD_WR_TYPE "altera_avalon_pio"
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
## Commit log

2015-12-08 versiones
2016-05-12 BASE Steri
2016-09-12 New Nextion, Audio, and Printer Driver 2016-09-12
2016-09-13 Version 2016-09-13, Alarma, Datalogger, GUI completa
2016-09-13 Version 2016-09-13, GUI completa
2016-09-14 Correciones del 2016/09/14, con codigos comentados
2016-09-14 Correciones del 2016/09/14, con codigos comentados y GUI actualizada
2016-09-14 Correciones del 2016/09/14, directorio linux
2016-09-14 README
2016-09-14 Correciones del 2016/09/14,

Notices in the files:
Base/V1_0_Test_pantalla/software/test_sterli_bsp/system.h:
Copyright (c) 2008
All rights reserved.
parts and their libraries:
SparkFun-Resistors: Licensing: Creative Commons ShareAlike 4.0 International - https://creativecommons.org/licenses/by-sa/4.0
